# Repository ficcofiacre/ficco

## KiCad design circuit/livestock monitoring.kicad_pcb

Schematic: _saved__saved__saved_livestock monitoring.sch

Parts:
C1, C2: C; C_1206_3216Metric_Pad1.42x1.75mm_HandSolder
R1: R; R_1206_3216Metric
SW1: SW_Push; SW_SPST_EVPBF
U1: ATtiny84-20SSU; SOIC-14_3.9x8.7mm_P1.27mm
U2: AMS1117-3.3; SOT-223-3_TabPin2
U3: MLX90615
U4: GPS-BN-220
U5: NRF24L01_Breakout; nRF24L01_Breakout

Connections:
CE: U1.6 (PA7), U5.3
CSN: U1.5 (PB2), U5.4
GND: C1.2, C2.2, SW1.1, U1.14 (GND), U2.1 (GND), U3.2, U4.1, U5.1
MISO: U1.8 (PA5), U5.6
MOSI: U1.7 (PA6), U5.7
RX: U1.13 (AREF/PA0), U4.2
SCK: U1.9 (PA4), U5.5
SCL: U1.11 (PA2), U3.3
SDA: U1.10 (PA3), U3.4
TX: U1.12 (PA1), U4.3
VIN: C1.1, R1.1, U1.1 (VCC), U2.3 (VI), U3.1, U4.4
VREG: C2.1, U2.2 (VO), U5.2
reset: R1.2, SW1.2, U1.4 (~RESET~/PB3)

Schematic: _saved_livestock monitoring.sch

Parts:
C1, C2: C; C_1206_3216Metric_Pad1.42x1.75mm_HandSolder
J1: AVR-ISP-6
R1: R; R_1206_3216Metric
SW1: SW_Push; SW_DIP_SPSTx01_Slide_6.7x4.1mm_W8.61mm_P2.54mm_LowProfile
U1: ATtiny84-20SSU; SOIC-14_3.9x8.7mm_P1.27mm
U2: AMS1117-3.3; SOT-223-3_TabPin2
U3: MLX90615
U4: GPS-BN-220
U5: NRF24L01_Breakout; nRF24L01_Breakout

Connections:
CE: U1.6 (PA7), U5.3
CSN: U1.5 (PB2), U5.4
GND: C1.2, C2.2, SW1.1, U1.14 (GND), U2.1 (GND), U3.2, U4.1, U5.1
MISO: U1.8 (PA5), U5.6
MOSI: U1.7 (PA6), U5.7
RX: U1.13 (AREF/PA0), U4.2
SCK: U1.9 (PA4), U5.5
SCL: U1.11 (PA2), U3.3
SDA: U1.10 (PA3), U3.4
TX: U1.12 (PA1), U4.3
VIN: C1.1, R1.1, U1.1 (VCC), U2.3 (VI), U3.1, U4.4
VREG: C2.1, U2.2 (VO), U5.2
reset: R1.2, SW1.2, U1.4 (~RESET~/PB3)

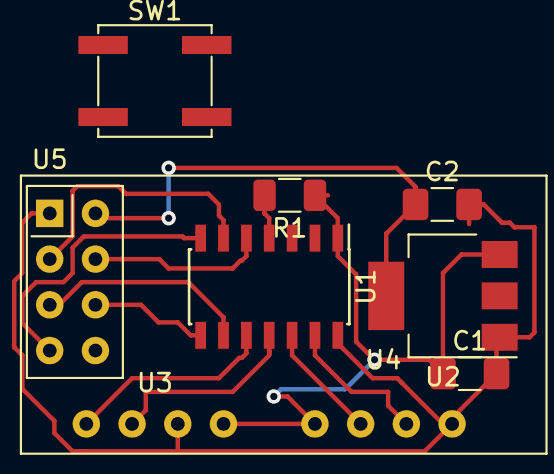
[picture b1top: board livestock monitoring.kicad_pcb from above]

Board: 2 copper layers, 9 parts (0 on the bottom side), 13 nets.

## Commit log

2018-11-08 circuit diagram and board
